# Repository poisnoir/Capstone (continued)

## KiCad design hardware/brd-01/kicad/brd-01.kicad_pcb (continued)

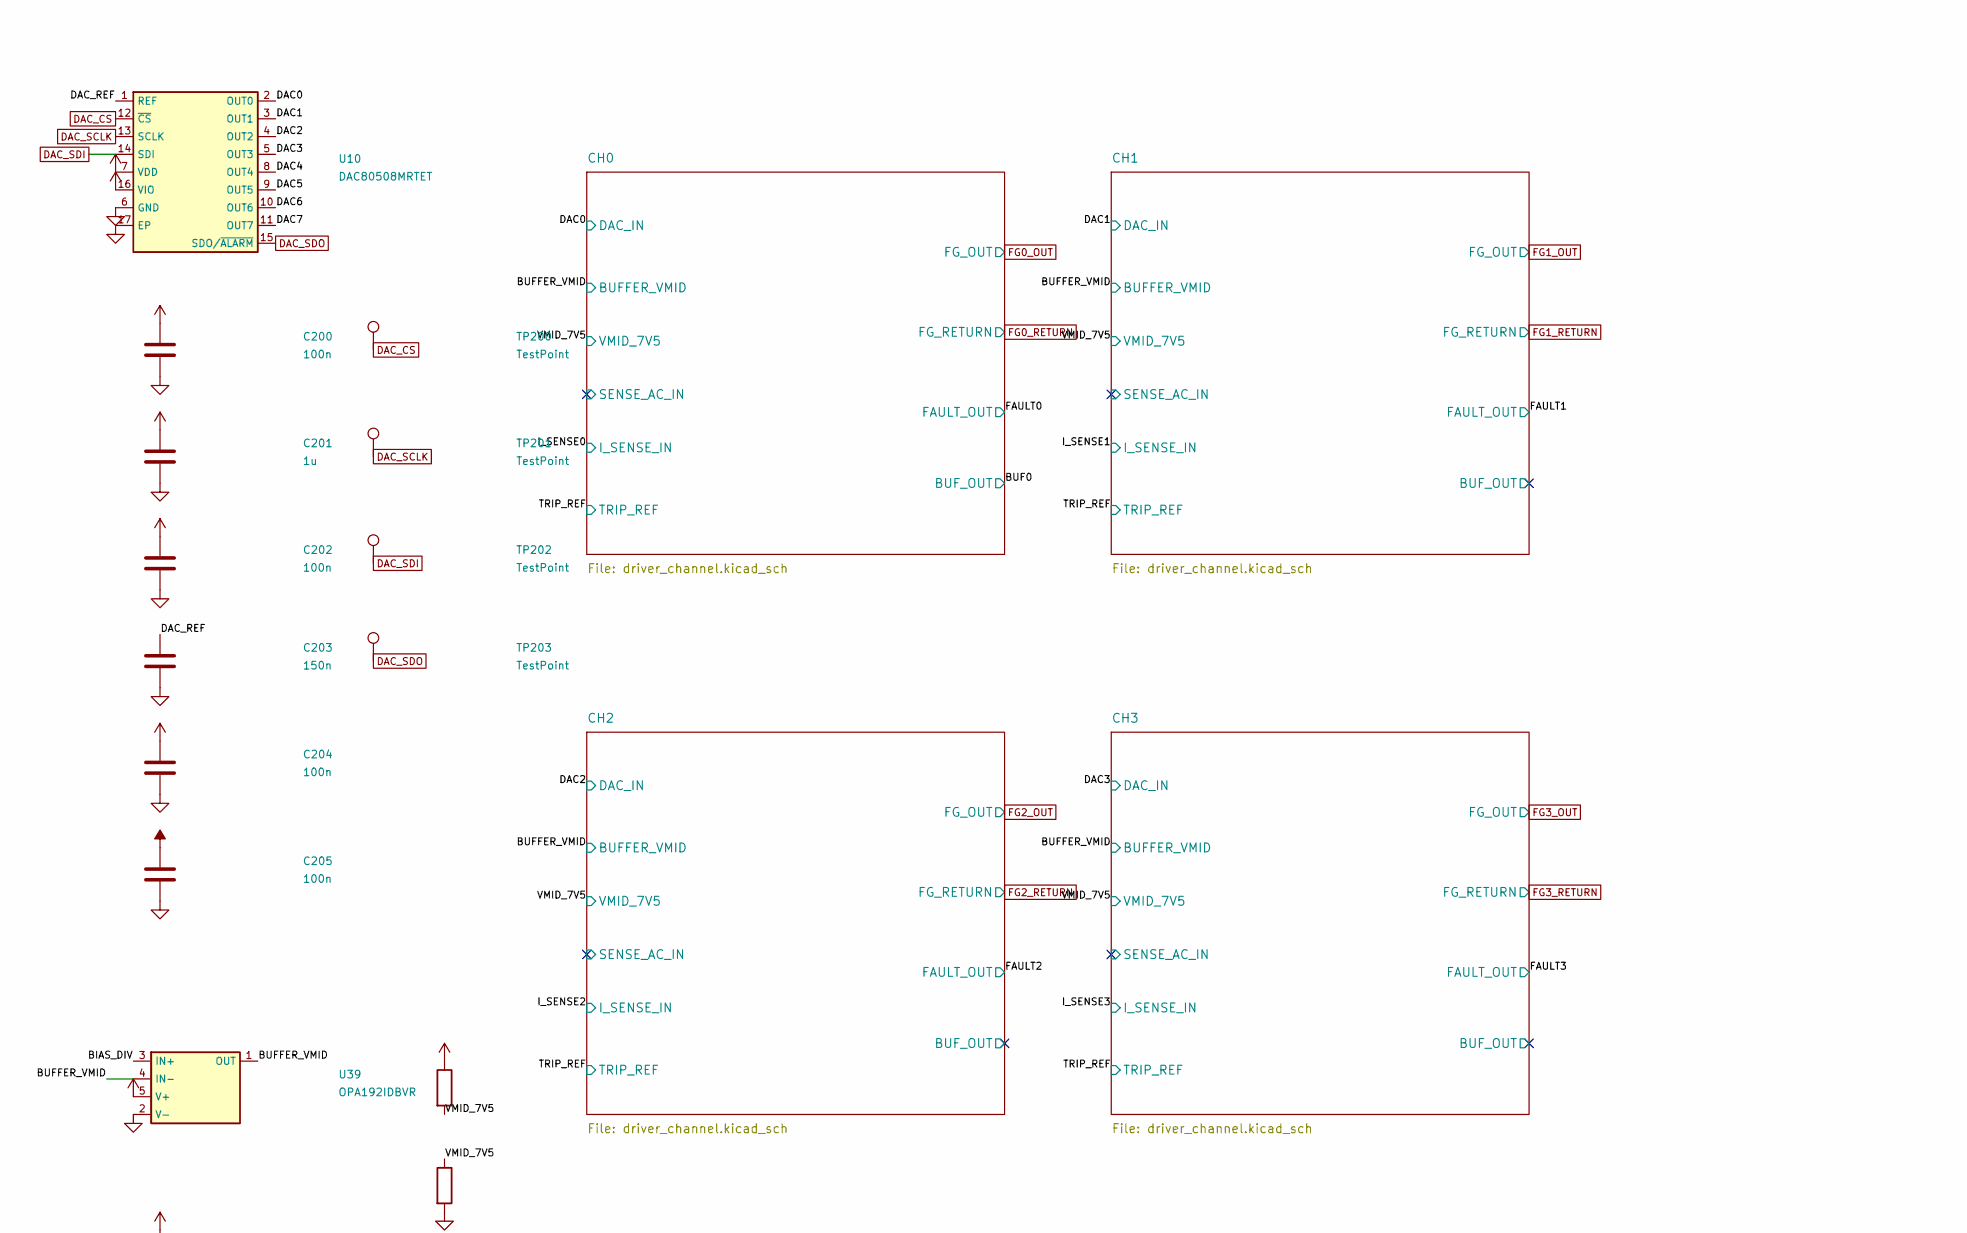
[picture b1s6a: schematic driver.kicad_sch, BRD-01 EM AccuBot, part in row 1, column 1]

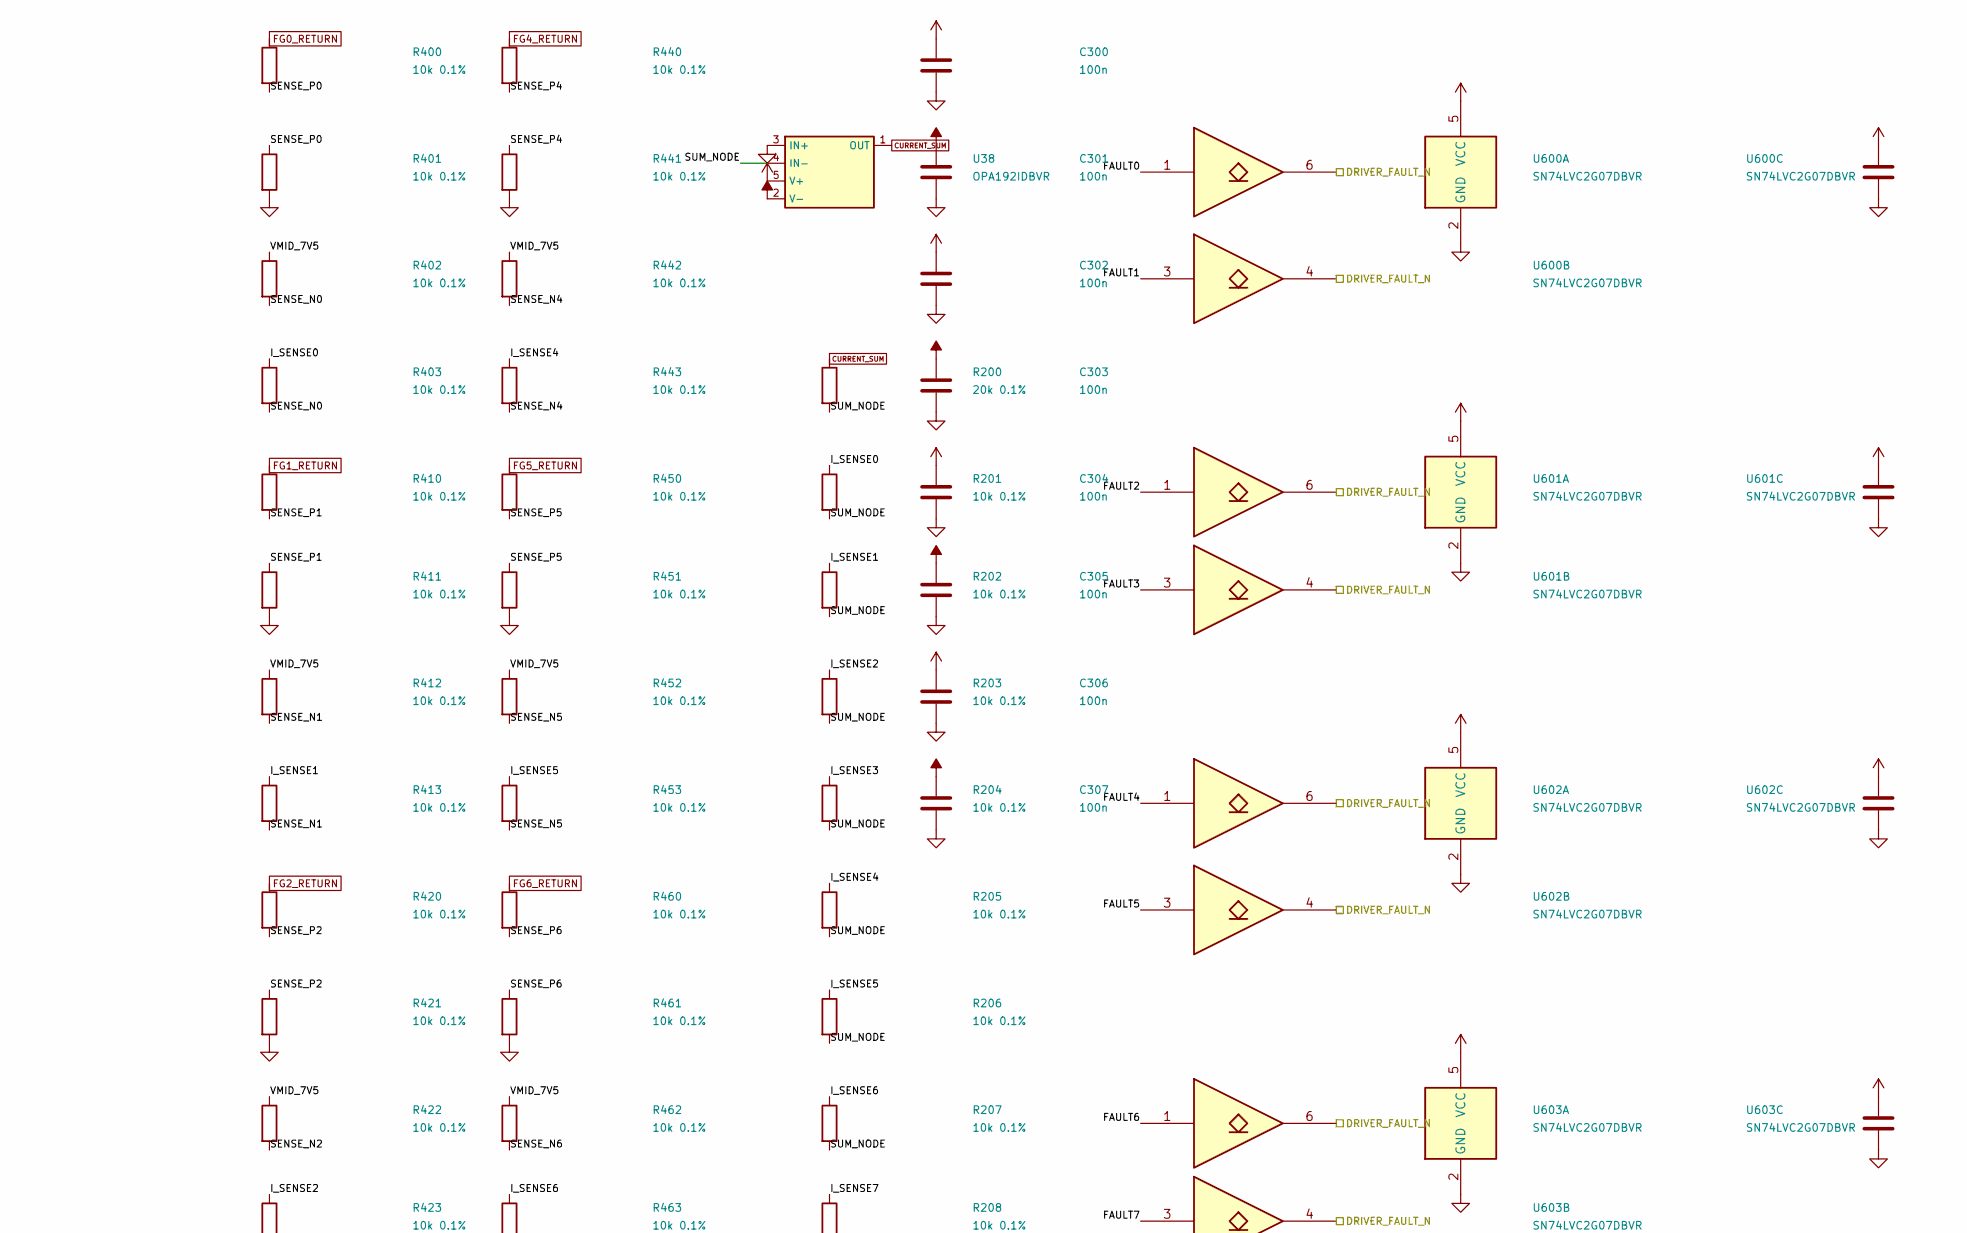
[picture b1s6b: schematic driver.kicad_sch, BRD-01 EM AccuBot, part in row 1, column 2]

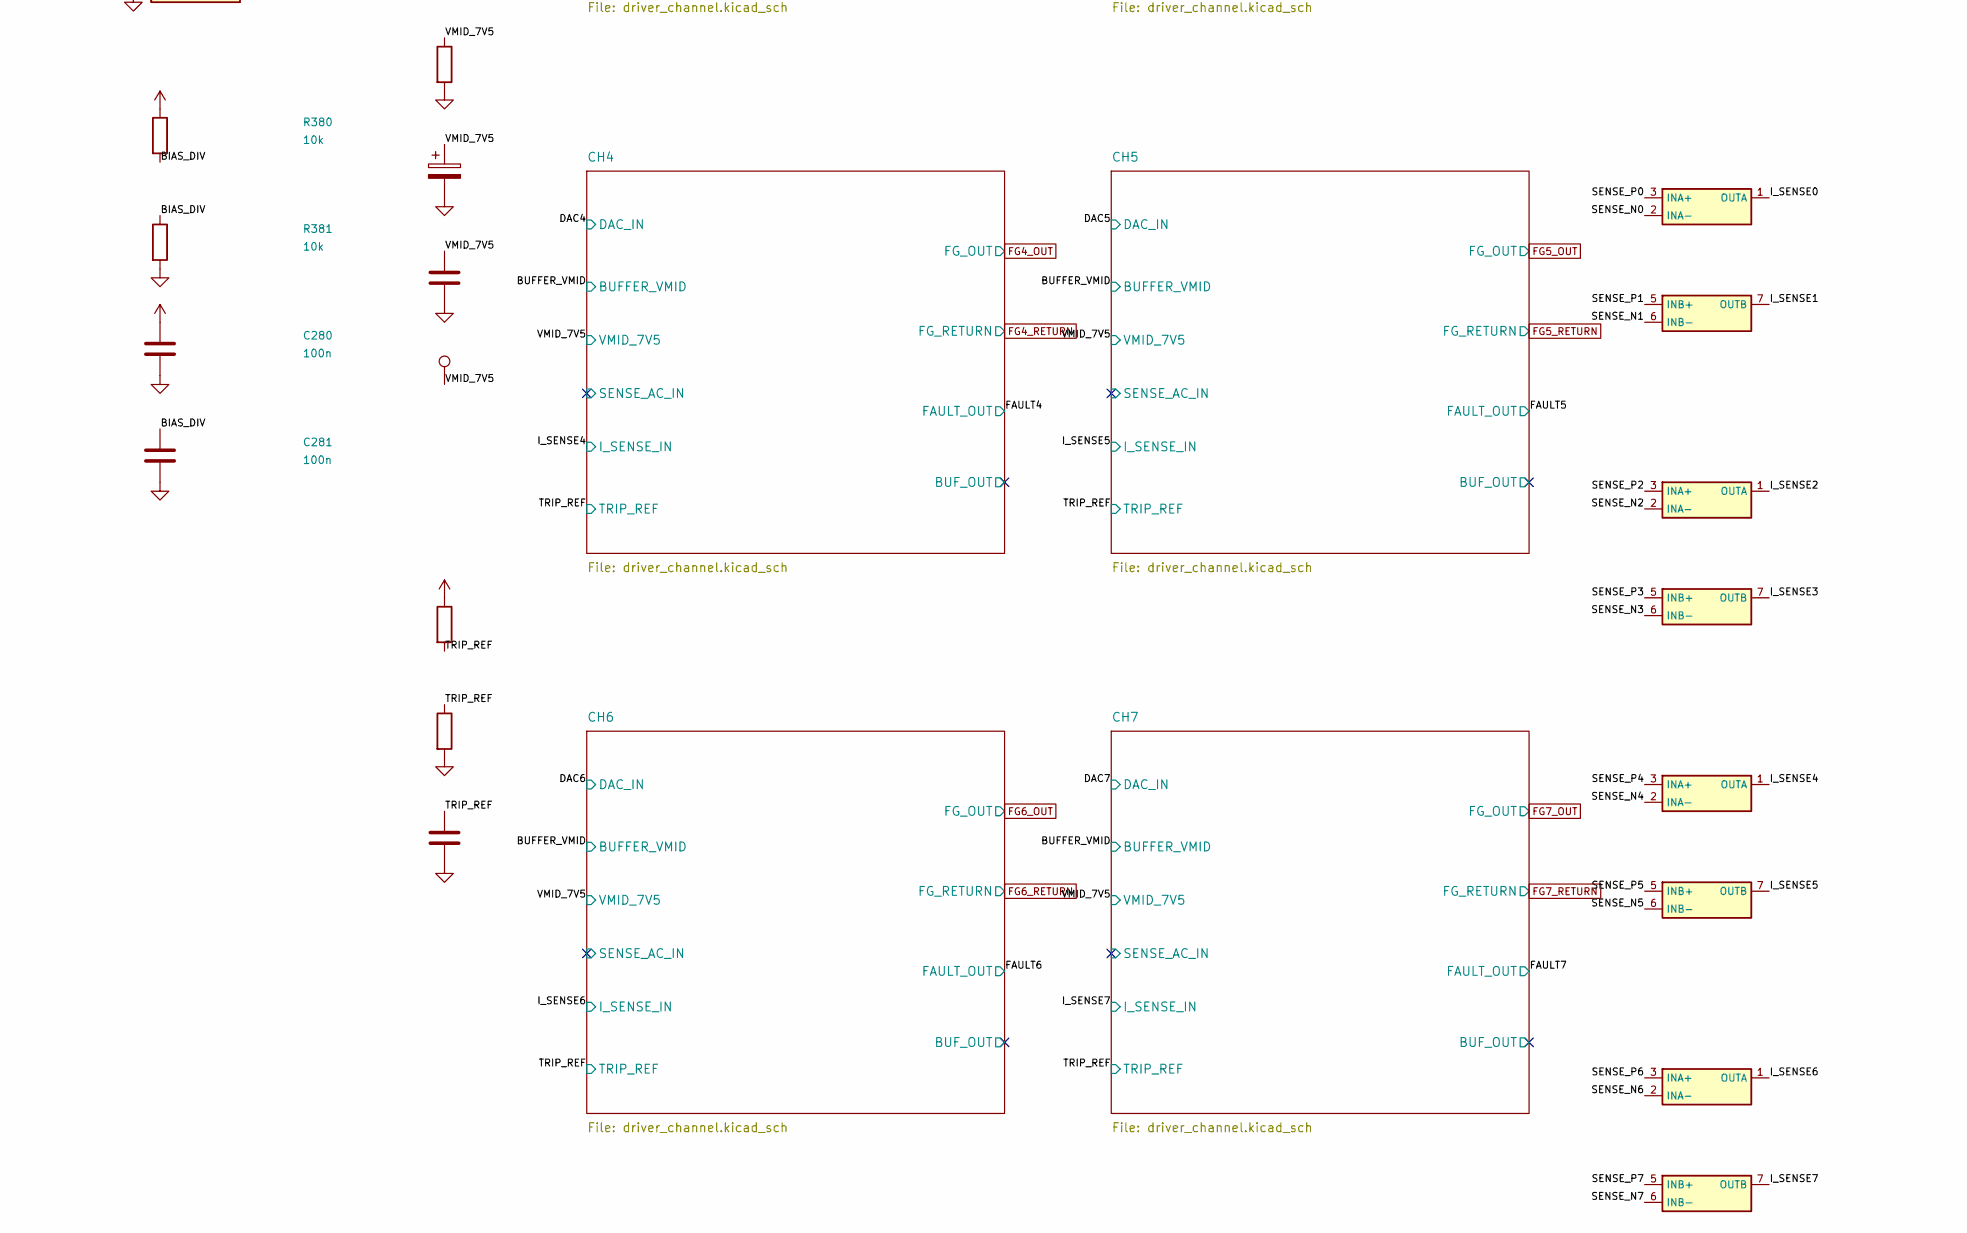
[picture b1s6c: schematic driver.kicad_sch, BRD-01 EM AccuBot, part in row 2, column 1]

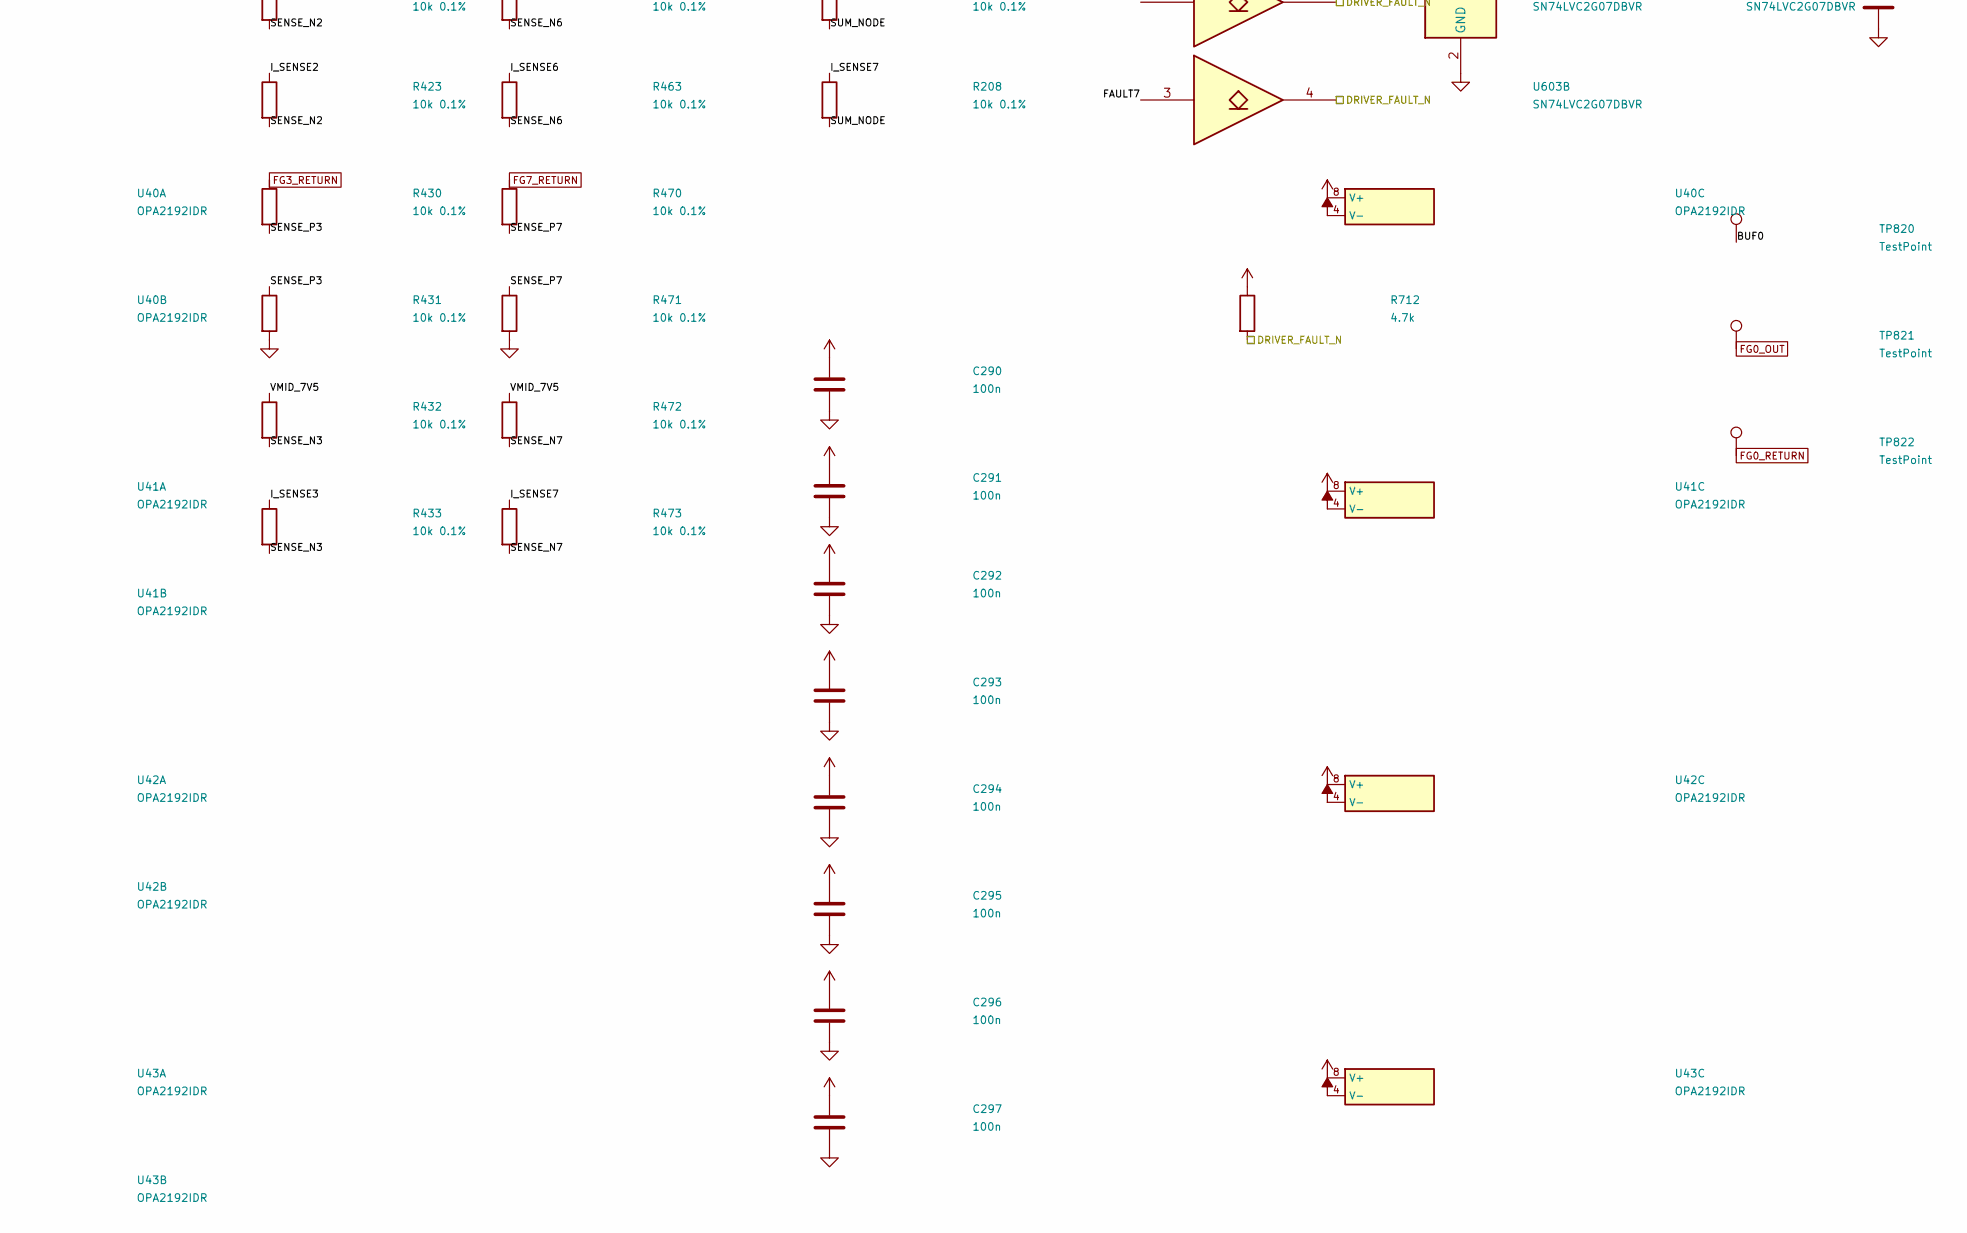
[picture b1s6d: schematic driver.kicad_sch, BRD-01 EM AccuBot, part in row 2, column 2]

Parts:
C200, C202, C204, C205, C280, C281, C283, C290, C291, C292, C293, C294, C295, C296, C297, C300, C301, C302, C303, C304, C305, C306, C307, C710, C711, C712, C713, C714: 100n; C_0603_1608Metric
C201: 1u; C_0805_2012Metric
C203: 150n; C_0603_1608Metric
C282: EEUFR1E102; CP_Radial_D10.0mm_P5.00mm
R200: 20k 0.1%; R_0603_1608Metric
R201, R202, R203, R204, R205, R206, R207, R208, R400, R401, R402, R403, R410, R411, R412, R413, R420, R421, R422, R423, R430, R431, R432, R433, R440, R441, R442, R443, R450, R451, R452, R453, R460, R461, R462, R463, R470, R471, R472, R473, R711: 10k 0.1%; R_0603_1608Metric
R380, R381, R382, R383: 10k; R_0603_1608Metric
R710: 52.3k 0.1%; R_0603_1608Metric
R712: 4.7k; R_0603_1608Metric
TP200, TP201, TP202, TP203: TestPoint; TestPoint_Pad_D1.0mm
TP820, TP821, TP822, TP823: TestPoint; TestPoint_Pad_D1.5mm
U10: DAC80508MRTET; Texas_RTE0016D_WQFN-16-1EP_3x3mm_P0.5mm_EP0.8x0.8mm
U38, U39: OPA192IDBVR; SOT-23-5
U40, U41, U42, U43: OPA2192IDR; SOIC-8_3.9x4.9mm_P1.27mm
U600, U601, U602, U603: SN74LVC2G07DBVR; SOT-23-6

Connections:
+3.3V: C202.1, C290.1, C291.1, C292.1, C293.1, C294.1, C295.1, C296.1, C297.1, C711.1, C712.1, C713.1, C714.1, R710.1, R712.1, U10.16 (VIO), U600.5 (VCC), U601.5 (VCC), U602.5 (VCC), U603.5 (VCC); also elsewhere on the board
+5V_EXC: C200.1, C201.1, U10.7 (VDD); also elsewhere on the board
+12VA: C204.1, C300.1, C302.1, C304.1, C306.1, U38.5 (V+), U40.8 (V+), U41.8 (V+), U42.8 (V+), U43.8 (V+); also elsewhere on the board
+15V_FUSED: C280.1, R380.1, R382.1, U39.5 (V+); also elsewhere on the board
-12VA: C205.1, C301.1, C303.1, C305.1, C307.1, U38.2 (V-), U40.4 (V-), U41.4 (V-), U42.4 (V-), U43.4 (V-); also elsewhere on the board
/DRIVER_FAULT_N: R712.2, U600.4, U600.6, U601.4, U601.6, U602.4, U602.6, U603.4, U603.6; also elsewhere on the board
/driver/BIAS_DIV: C281.1, R380.2, R381.1, U39.3 (IN+)
/driver/BUF0: TP820.1 (1_1); also elsewhere on the board
/driver/BUFFER_VMID: U39.1 (OUT), U39.4 (IN-); also elsewhere on the board
/driver/DAC0: U10.2 (OUT0); also elsewhere on the board
/driver/DAC1: U10.3 (OUT1); also elsewhere on the board
/driver/DAC2: U10.4 (OUT2); also elsewhere on the board
/driver/DAC3: U10.5 (OUT3); also elsewhere on the board
/driver/DAC4: U10.8 (OUT4); also elsewhere on the board
/driver/DAC5: U10.9 (OUT5); also elsewhere on the board
/driver/DAC6: U10.10 (OUT6); also elsewhere on the board
/driver/DAC7: U10.11 (OUT7); also elsewhere on the board
/driver/DAC_REF: C203.1, U10.1 (REF)
/driver/FAULT0: U600.1; also elsewhere on the board
/driver/FAULT1: U600.3; also elsewhere on the board
/driver/FAULT2: U601.1; also elsewhere on the board
/driver/FAULT3: U601.3; also elsewhere on the board
/driver/FAULT4: U602.1; also elsewhere on the board
/driver/FAULT5: U602.3; also elsewhere on the board
/driver/FAULT6: U603.1; also elsewhere on the board
/driver/FAULT7: U603.3; also elsewhere on the board
/driver/I_SENSE0: R201.1, R403.1, U40.1 (OUTA); also elsewhere on the board
/driver/I_SENSE1: R202.1, R413.1, U40.7 (OUTB); also elsewhere on the board
/driver/I_SENSE2: R203.1, R423.1, U41.1 (OUTA); also elsewhere on the board
/driver/I_SENSE3: R204.1, R433.1, U41.7 (OUTB); also elsewhere on the board
/driver/I_SENSE4: R205.1, R443.1, U42.1 (OUTA); also elsewhere on the board
/driver/I_SENSE5: R206.1, R453.1, U42.7 (OUTB); also elsewhere on the board
/driver/I_SENSE6: R207.1, R463.1, U43.1 (OUTA); also elsewhere on the board
/driver/I_SENSE7: R208.1, R473.1, U43.7 (OUTB); also elsewhere on the board
/driver/SENSE_N0: R402.2, R403.2, U40.2 (INA-)
/driver/SENSE_N1: R412.2, R413.2, U40.6 (INB-)
/driver/SENSE_N2: R422.2, R423.2, U41.2 (INA-)
/driver/SENSE_N3: R432.2, R433.2, U41.6 (INB-)
/driver/SENSE_N4: R442.2, R443.2, U42.2 (INA-)
/driver/SENSE_N5: R452.2, R453.2, U42.6 (INB-)
/driver/SENSE_N6: R462.2, R463.2, U43.2 (INA-)
/driver/SENSE_N7: R472.2, R473.2, U43.6 (INB-)
/driver/SENSE_P0: R400.2, R401.1, U40.3 (INA+)
/driver/SENSE_P1: R410.2, R411.1, U40.5 (INB+)
/driver/SENSE_P2: R420.2, R421.1, U41.3 (INA+)
/driver/SENSE_P3: R430.2, R431.1, U41.5 (INB+)
/driver/SENSE_P4: R440.2, R441.1, U42.3 (INA+)
/driver/SENSE_P5: R450.2, R451.1, U42.5 (INB+)
/driver/SENSE_P6: R460.2, R461.1, U43.3 (INA+)
/driver/SENSE_P7: R470.2, R471.1, U43.5 (INB+)
/driver/SUM_NODE: R200.2, R201.2, R202.2, R203.2, R204.2, R205.2, R206.2, R207.2, R208.2, U38.4 (IN-)
/driver/TRIP_REF: C710.1, R710.2, R711.1; also elsewhere on the board
/driver/VMID_7V5: C282.1, C283.1, R382.2, R383.1, R402.1, R412.1, R422.1, R432.1, R442.1, R452.1, R462.1, R472.1, TP823.1 (1_1); also elsewhere on the board
CURRENT_SUM: R200.1, U38.1 (OUT); also elsewhere on the board
DAC_CS: TP200.1 (1_1), U10.12 (~CS); also elsewhere on the board
DAC_SCLK: TP201.1 (1_1), U10.13 (SCLK); also elsewhere on the board
DAC_SDI: TP202.1 (1_1), U10.14 (SDI); also elsewhere on the board
DAC_SDO: TP203.1 (1_1), U10.15 (SDO/~ALARM); also elsewhere on the board
FG0_OUT: TP821.1 (1_1); also elsewhere on the board
FG0_RETURN: R400.1, TP822.1 (1_1); also elsewhere on the board
FG1_RETURN: R410.1; also elsewhere on the board
FG2_RETURN: R420.1; also elsewhere on the board
FG3_RETURN: R430.1; also elsewhere on the board
FG4_RETURN: R440.1; also elsewhere on the board
FG5_RETURN: R450.1; also elsewhere on the board
FG6_RETURN: R460.1; also elsewhere on the board
FG7_RETURN: R470.1; also elsewhere on the board
GND: C200.2, C201.2, C202.2, C203.2, C204.2, C205.2, C280.2, C281.2, C282.2, C283.2, C290.2, C291.2, C292.2, C293.2, C294.2, C295.2, C296.2, C297.2, C300.2, C301.2, C302.2, C303.2, C304.2, C305.2, C306.2, C307.2, C710.2, C711.2, C712.2, C713.2, C714.2, R381.2, R383.2, R401.2, R411.2, R421.2, R431.2, R441.2, R451.2, R461.2, R471.2, R711.2, U10.6 (GND), U10.17 (EP), U38.3 (IN+), U39.2 (V-), U600.2 (GND), U601.2 (GND), U602.2 (GND), U603.2 (GND); also elsewhere on the board
